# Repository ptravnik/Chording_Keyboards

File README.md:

This project contains files for K-Chord and other chording keyboards.

[1] Why chording?
Medics may disagree, but it seems that constantly bending fingers back and forth while touch-typing by the 10-finger method is the second reason (besides the poor posture) why people have carpal tunnel syndrome. In such sense, "ergonomic" keyboards help just a little if not at all. There are numerous mechanical keyboard on the market. Cherry switches and their clones offer performance superior to the film keyboards, but the idea is pretty much the same: 10 fingers, 60 or so switches; once in a while one must reach that switch in the galaxy far, far away with the left or right pinky!

The main drive for this project was not to type faster than speech, a a steno professionals do, but to type at reasonable speed whole day with no strain. In practice, I seldom exceed 20 WPM (just cannot think GOOD code that fast!), but can maintain this for many hours - without ever bending a finger. The keyboard has 8 finger buttons and 6 thumb buttons. The fingers always remain in the "home" position; there is nothing else, but the home position. The thumbs move as the nature intended: in the main (grip) joint, with the zero second joint bending. By shifting the fingers down 1 inch, a set of two analog joysticks, three mouse buttons and 4 arrow keys is accessible. Together with the left thumb, the arrow keys provide full set of cursor movements, including page-up and page-down.

This is the third version of my chording keyboard. The work in progress is described on the Hackaday site https://hackaday.io/project/25386-chording-hybrid-keyboard. The experience has been good so far. I use it now as my primary input method, for text writing, programming, and operating specialized software.

[2] Building a chording keyboard.
This project depository contains:

(a) the full electronics description as a set of three PCBs,

(b) A set of CNC files for making a body, and

(c) the code for Arduino Micro, which drives the entire project. No modification is required at the operating system side; the keyboard works as an off-the-shelf USB keyboard. It has been tested on Windows and Linux extensively.

To order PCBs, simply use Gerber files provided or modify KiCAD files to you liking. The body can be machined on a CNC router (recommeneded), 3-D printed or laser-cut (some compromizes on the shape). To build the firmware, copy the .ino folder and use Arduino IDE to compile and upload (put any macros of your liking into the macros.h file).

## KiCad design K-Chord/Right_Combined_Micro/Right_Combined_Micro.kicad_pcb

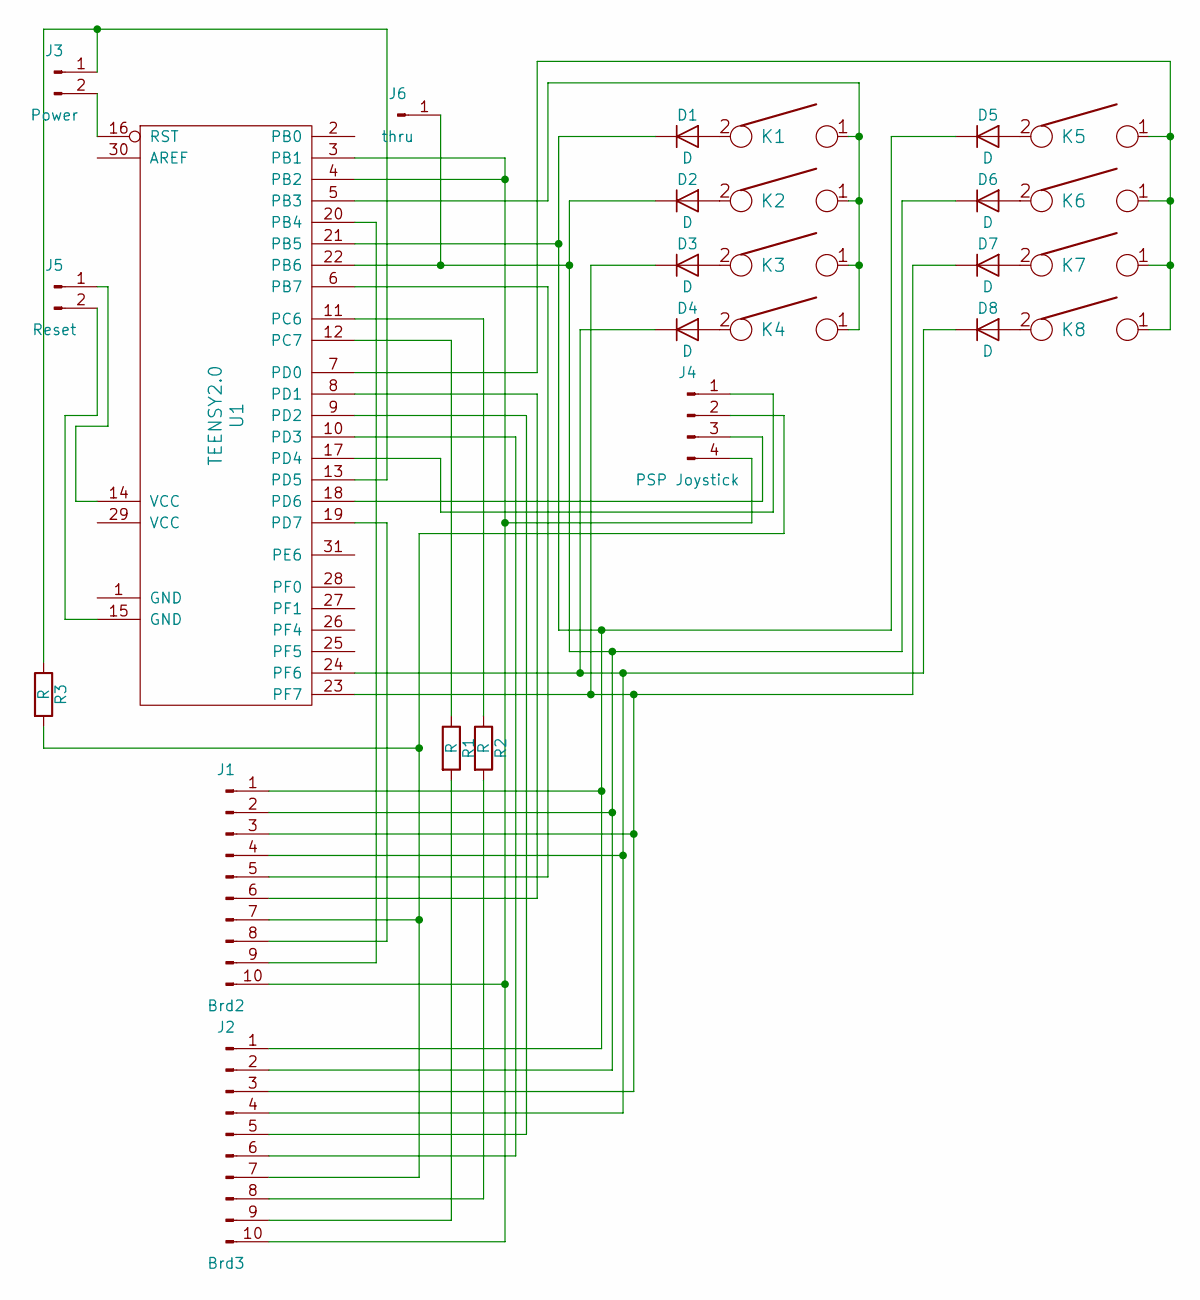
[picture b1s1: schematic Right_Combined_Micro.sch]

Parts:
D1, D2, D3, D4, D5, D6, D7, D8: D; D_SOD123_axial
J1: Brd2; Pin_Header_Straight_1x10_Pitch2.54mm
J2: Brd3; Pin_Header_Straight_1x10_Pitch2.54mm
J3: Power; Pin_Header_Straight_1x02_Pitch2.54mm
J4: PSP Joystick; Pin_Header_Straight_1x04_Pitch2.54mm
J5: Reset; Pin_Header_Straight_1x02_Pitch2.54mm
J6: thru; Pin_Header_Straight_1x01_Pitch2.54mm
K1, K2, K3, K4, K5, K6, K7, K8: KEYSW; Mx_Alps_100
R1, R2, R3: R; Resistor_SMD+THTuniversal_2512_RM10_HandSoldering
U1: TEENSY2.0; Pro_Micro

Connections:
unnamed: D1.1 (K), D5.1 (K), J1.1, J2.1, U1.21 (PB5)
unnamed: D1.2 (A), K1.2
unnamed: D2.1 (K), D6.1 (K), J1.2, J2.2, J6.1, U1.22 (PB6)
unnamed: D2.2 (A), K2.2
unnamed: D3.1 (K), D7.1 (K), J1.3, J2.3, U1.23 (PF7)
unnamed: D3.2 (A), K3.2
unnamed: D4.1 (K), D8.1 (K), J1.4, J2.4, U1.24 (PF6)
unnamed: D4.2 (A), K4.2
unnamed: D5.2 (A), K5.2
unnamed: D6.2 (A), K6.2
unnamed: D7.2 (A), K7.2
unnamed: D8.2 (A), K8.2
unnamed: J1.5, U1.6 (PB7)
unnamed: J1.6, U1.8 (PD1)
unnamed: J1.7, J2.7, J4.2, R3.2
unnamed: J1.8, U1.19 (PD7)
unnamed: J1.9, U1.20 (PB4)
unnamed: J1.10, J2.10, J4.4, U1.3 (PB1), U1.4 (PB2)
unnamed: J2.5, U1.9 (PD2)
unnamed: J2.6, U1.10 (PD3)
unnamed: J2.8, R2.2
unnamed: J2.9, R1.2
unnamed: J3.1, R3.1, U1.13 (PD5)
unnamed: J3.2, U1.16 (RST)
unnamed: J4.1, U1.17 (PD4)
unnamed: J4.3, U1.18 (PD6)
unnamed: J5.1, U1.14 (VCC)
unnamed: J5.2, U1.15 (GND)
unnamed: K1.1, K2.1, K3.1, K4.1, U1.5 (PB3)
unnamed: K5.1, K6.1, K7.1, K8.1, U1.7 (PD0)
unnamed: R1.1, U1.12 (PC7)
unnamed: R2.1, U1.11 (PC6)

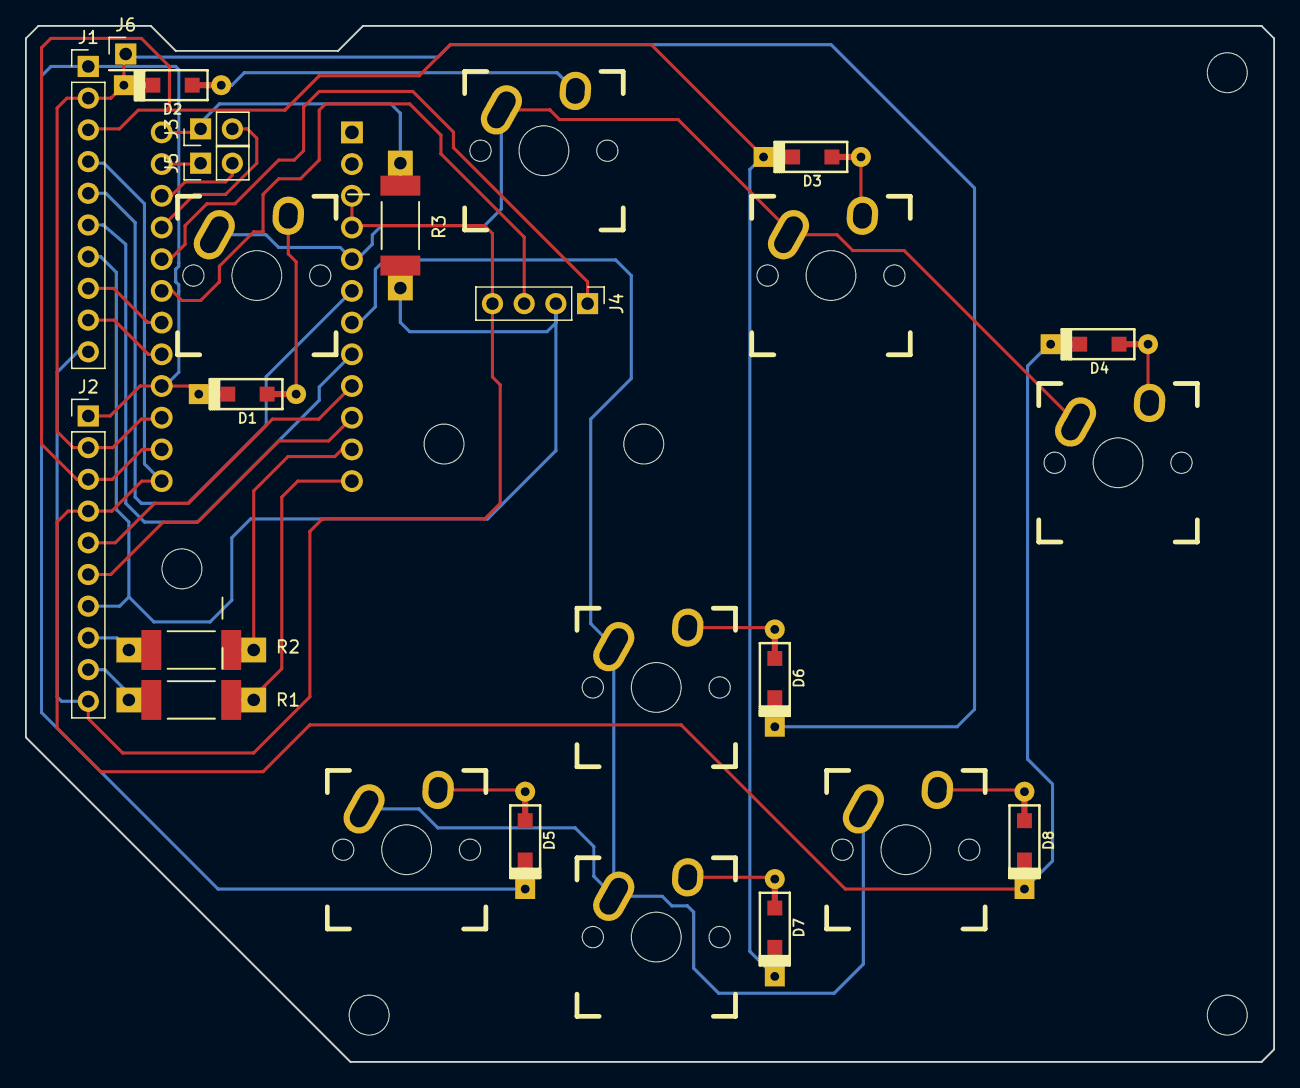
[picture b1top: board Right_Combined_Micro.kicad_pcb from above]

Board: 2 copper layers, 100.0 x 83.0 mm, 26 parts (1 on the bottom side), 32 nets.

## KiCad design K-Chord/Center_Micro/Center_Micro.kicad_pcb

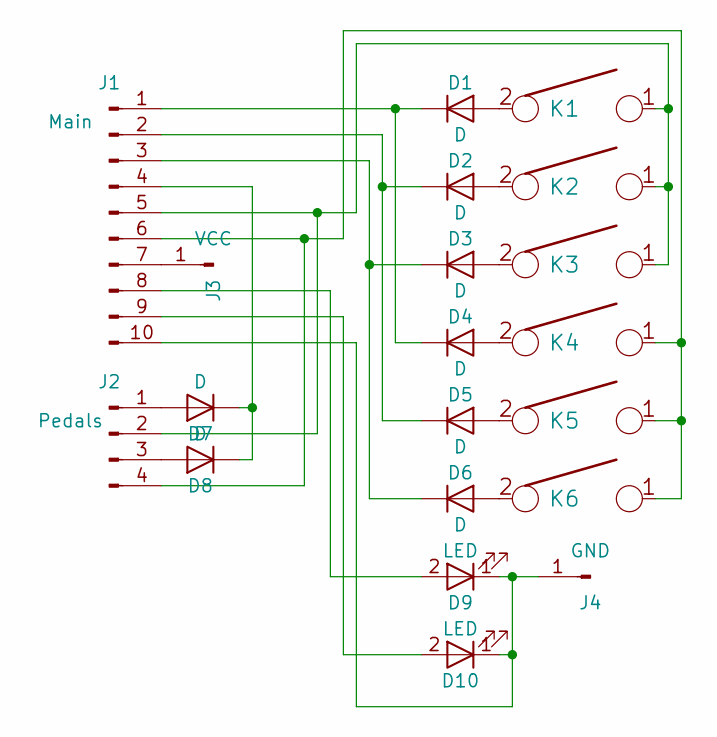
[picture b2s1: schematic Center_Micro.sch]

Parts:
D1, D2, D3, D4, D5, D6, D7, D8: D; D_SOD123_axial
D9, D10: LED; LED_TH
J1: Main; Pin_Header_Angled_1x10_Pitch2.54mm
J2: Pedals; Pin_Header_Angled_1x04_Pitch2.54mm
J3: VCC; Pin_Header_Straight_1x01_Pitch2.54mm
J4: GND; Pin_Header_Straight_1x01_Pitch2.54mm
K1, K2, K3, K4, K5, K6: KEYSW; Mx_Alps_100

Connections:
unnamed: D1.1 (K), D4.1 (K), J1.1
unnamed: D1.2 (A), K1.2
unnamed: D2.1 (K), D5.1 (K), J1.2
unnamed: D2.2 (A), K2.2
unnamed: D3.1 (K), D6.1 (K), J1.3
unnamed: D3.2 (A), K3.2
unnamed: D4.2 (A), K4.2
unnamed: D5.2 (A), K5.2
unnamed: D6.2 (A), K6.2
unnamed: D7.1 (K), D8.1 (K), J1.4
unnamed: D7.2 (A), J2.1
unnamed: D8.2 (A), J2.3
unnamed: D9.2 (A), J1.8
unnamed: D9.1 (K), D10.1 (K), J1.10, J4.1
unnamed: D10.2 (A), J1.9
unnamed: J1.5, J2.2, K1.1, K2.1, K3.1
unnamed: J1.6, J2.4, K4.1, K5.1, K6.1
unnamed: J1.7, J3.1

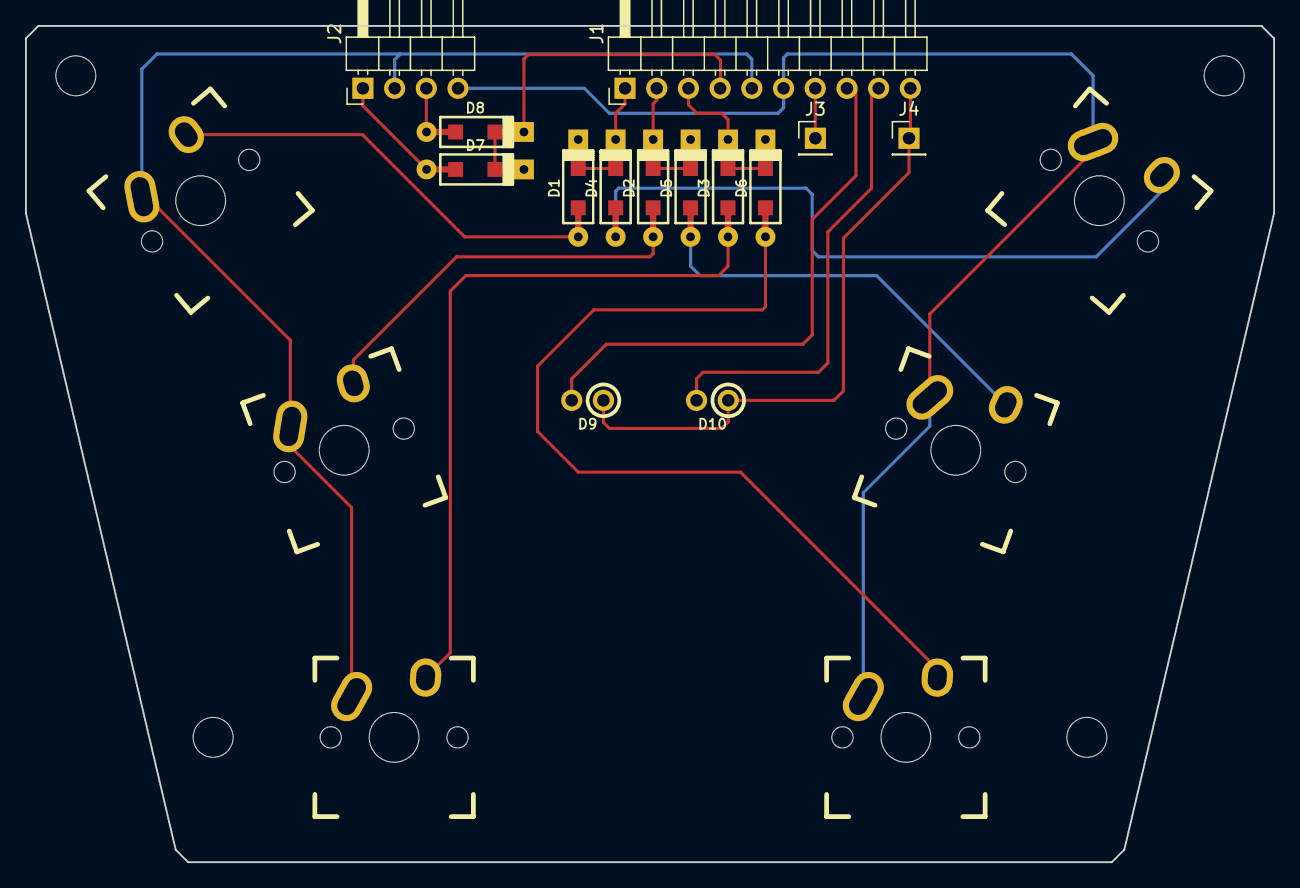
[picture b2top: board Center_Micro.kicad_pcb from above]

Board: 2 copper layers, 100.0 x 67.0 mm, 20 parts (0 on the bottom side), 18 nets.

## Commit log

2019-07-07 Version 9 of the keyboard sketch
    Compile directly with Arduino IDE.
2019-07-07 Separated sketch into readable blocks
2019-07-07 KiCAD files for PCBs
2019-07-07 Libraries used for kiCAD
2019-07-07 Added readme
2019-07-07 Added pictures
2019-07-07 Stl files for printing or machining
